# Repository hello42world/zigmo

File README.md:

# Intro
ZigMo is a 4 channel Zigbee soil moisture meter.  The project pursues 2 goals:
* Hardware: Attempt some very basic electric engineering and build a Zigbee device based on a custom PCB.
* Software: Write a custom firmware for the device that would make the Zigbee thing work.  

# Description
The concept is pretty simple. It is a Zigbee end device with 4 capacitive wire connected moisture sensors that you could stick into 4 nearby flower pots and monitor moisture levels in all of them with a single device.

This is what it looks like in Home Assistant:

The device is based on a popular CC2530 module that can be bought off Aliexpress for about $3. Custom PCB part handles battery power, routes connections to individual moisture sensors, provides debug connectors and implements user interface - a LED and a button.

# Build notes
### PCB:
The PCB was designed in KiCad and then ordered from JLCPCB. All parts are common and can be ordered from your favorite parts supplier.

**Note**: I know nothing about electric engineering and have no experience with PCB design. I just watched some video on Youtube on how to do it.

### Firmware:
The firmware is based on Zstack 3.0.2. It simply queries the moisture sensors and measures battery voltage every 5 minutes.

ZStack SDK is available for free from Texas Instruments. It contains several examples and even a guide on how to branch your own project off one of those examples (Z-Stack 3.0 Sample Application User's Guide.pdf). 
The most challenging part IMO is getting the IDE/Compiler. ZStack 3.0.2 applications should be built using IAR studio for 8051 processors version 10.20. This IDE is not free, however a free trial is available. You may find other ways of getting it if you search hard enough.

# See also
- Book: Drew Gislason - "Zigbee Wireless Networking"
- Very cool and super detailed series of posts on how to build a Zigbee device from scratch based on the NXP Zigbee stack: https://github.com/grafalex82/hellozigbee
- A bunch of ZStack Zigbee projects built at very professional level: https://github.com/diyruz

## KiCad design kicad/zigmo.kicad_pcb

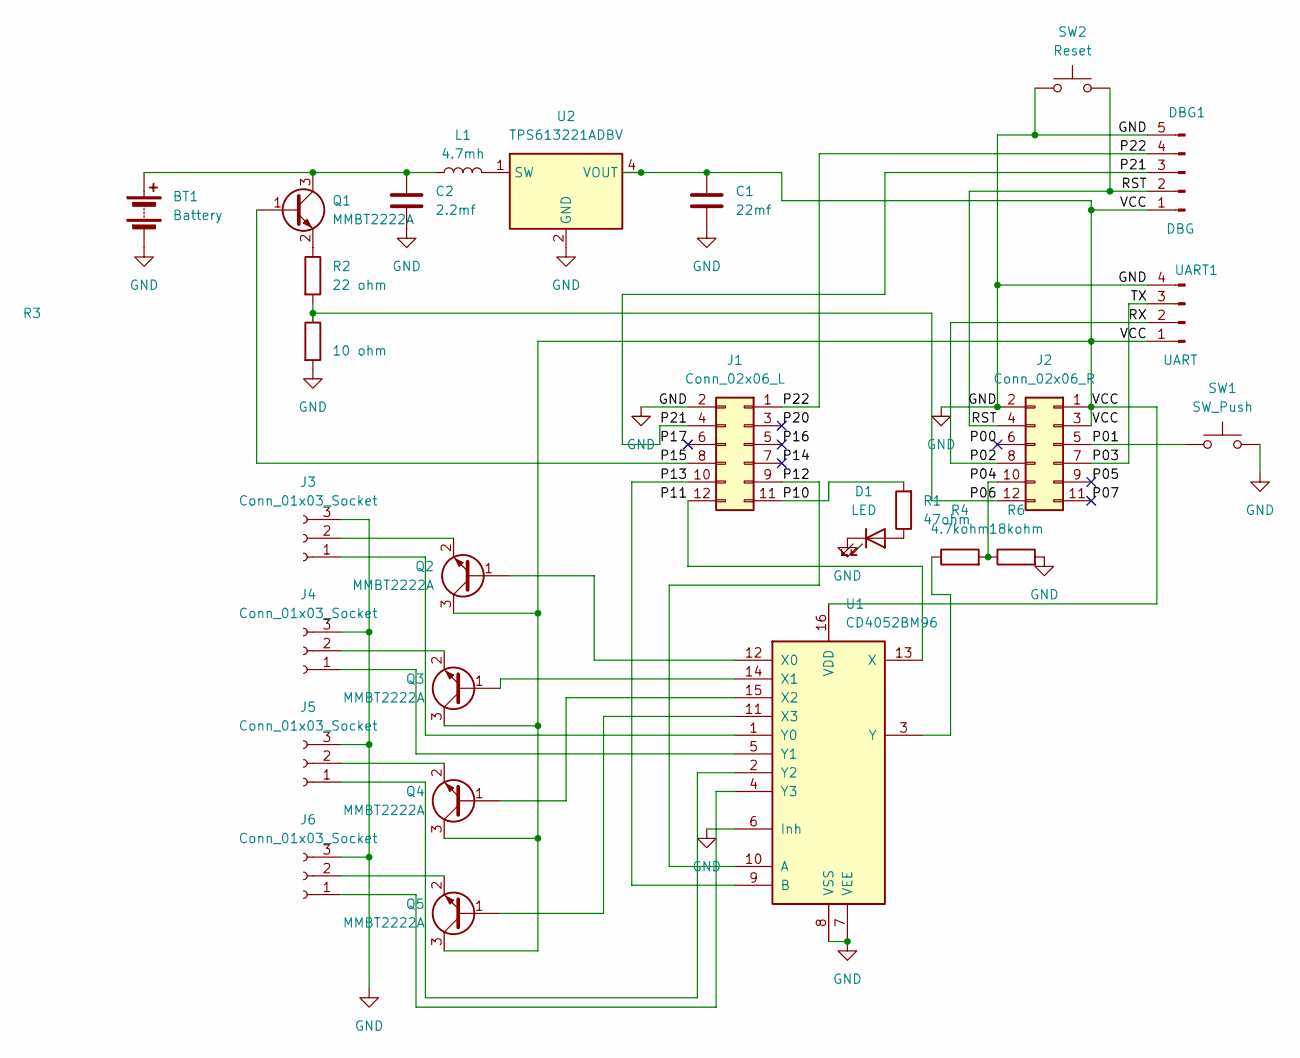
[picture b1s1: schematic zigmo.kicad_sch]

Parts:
BT1: Battery; BatteryHolder_Keystone_2462_2xAA
C1: 22mf; C_0805_2012Metric_Pad1.18x1.45mm_HandSolder
C2: 2.2mf; C_0805_2012Metric_Pad1.18x1.45mm_HandSolder
D1: LED; LED_D3.0mm
DBG1: DBG; PinHeader_1x05_P2.54mm_Vertical
J1: Conn_02x06_L; PinSocket_2x06_P2.54mm_Vertical
J2: Conn_02x06_R; PinSocket_2x06_P2.54mm_Vertical
J3, J4, J5, J6: Conn_01x03_Socket; JST_XH_B3B-XH-A_1x03_P2.50mm_Vertical
L1: 4.7mh; L_1008_2520Metric_Pad1.43x2.20mm_HandSolder
Q1, Q2, Q3, Q4, Q5: MMBT2222A; SOT-23
R1: 47ohm; R_0805_2012Metric_Pad1.20x1.40mm_HandSolder
R2: 22 ohm; R_0805_2012Metric_Pad1.20x1.40mm_HandSolder
R3: 10 ohm; R_0805_2012Metric_Pad1.20x1.40mm_HandSolder
R4: 4.7kohm; R_0805_2012Metric_Pad1.20x1.40mm_HandSolder
R6: 18kohm; R_0805_2012Metric_Pad1.20x1.40mm_HandSolder
SW1: SW_Push; SW_SPST_B3U-1000P
SW2: Reset; SW_SPST_B3U-1000P
U1: CD4052BM96; SO-16_3.9x9.9mm_P1.27mm
U2: TPS613221ADBV; SOT-23-5
UART1: UART; PinHeader_1x04_P2.54mm_Vertical

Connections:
/P00: J2.6
/P01: J2.5, SW1.1
/P02: J2.8, UART1.2; also elsewhere on the board
/P03: J2.7, UART1.3; also elsewhere on the board
/P04: J2.10, R4.2, R6.1
/P05: J2.9
/P06: J2.12, R2.2, R3.1
/P07: J2.11
/P10: J1.11, R1.2
/P11: J1.12, U1.13 (X)
/P12: J1.9, U1.10 (A)
/P13: J1.10, U1.9 (B)
/P14: J1.7
/P15: J1.8, Q1.1 (B)
/P16: J1.5
/P17: J1.6
/P20: J1.3
/P21: DBG1.3, J1.4; also elsewhere on the board
/P22: DBG1.4, J1.1; also elsewhere on the board
/RST: DBG1.2, J2.4, SW2.2; also elsewhere on the board
/VCC: C1.1, DBG1.1, J2.1, J2.3, Q2.3 (C), Q3.3 (C), Q4.3 (C), Q5.3 (C), U1.16 (VDD), U2.4 (VOUT), UART1.1; also elsewhere on the board
GND: BT1.2 (-), C1.2, C2.2, D1.1 (K), DBG1.5, J1.2, J2.2, J3.3, J4.3, J5.3, J6.3, R3.2, R6.2, SW1.2, SW2.1, U1.6 (Inh), U1.7 (VEE), U1.8 (VSS), U2.2 (GND), UART1.4; also elsewhere on the board
unnamed: BT1.1 (+), C2.1, L1.1, Q1.3 (C)
unnamed: D1.2 (A), R1.1
unnamed: J3.1, U1.1 (Y0)
unnamed: J3.2, Q2.2 (E)
unnamed: J4.1, U1.5 (Y1)
unnamed: J4.2, Q3.2 (E)
unnamed: J5.1, U1.2 (Y2)
unnamed: J5.2, Q4.2 (E)
unnamed: J6.1, U1.4 (Y3)
unnamed: J6.2, Q5.2 (E)
unnamed: Q1.2 (E), R2.1
unnamed: Q2.1 (B), U1.12 (X0)
unnamed: Q3.1 (B), U1.14 (X1)
unnamed: Q4.1 (B), U1.15 (X2)
unnamed: Q5.1 (B), U1.11 (X3)
unnamed: R4.1, U1.3 (Y)
unnamed: L1.2, U2.1 (SW)

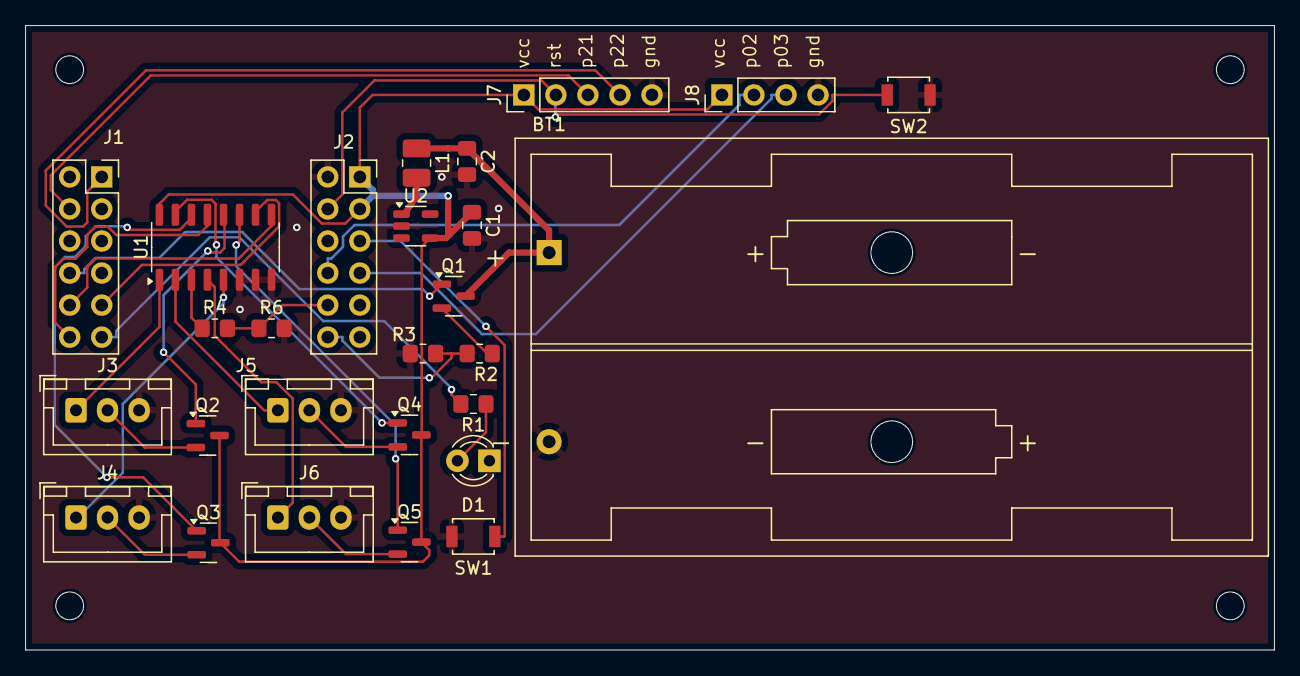
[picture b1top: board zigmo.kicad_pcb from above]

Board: 2 copper layers, 99.0 x 49.5 mm, 31 parts (0 on the bottom side), 32 nets.

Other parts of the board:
J7: DBG; PinHeader_1x05_P2.54mm_Vertical
J8: UART; PinHeader_1x04_P2.54mm_Vertical
REF1, REF2, REF3, REF4: MountingHole_2.2mm_M2

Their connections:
/P02: J8.2; also elsewhere on the board
/P03: J8.3; also elsewhere on the board
/P21: J7.3; also elsewhere on the board
/P22: J7.4; also elsewhere on the board
/RST: J7.2; also elsewhere on the board
/VCC: J7.1, J8.1; also elsewhere on the board
GND: J7.5, J8.4; also elsewhere on the board

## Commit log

2024-07-02 Try running all endpoints in 1 task
2024-07-03 Initial sketch of sensor array code
2024-07-03 Code cleanup
2024-07-03 Try multiple sensors in array
2024-07-07 Sensor value update works (dummy)
2024-07-29 Dummy attr update (on timer)
2024-07-29 Custom HAL compiles (not tested)
2024-07-30 debug stuff
2024-08-04 Restart button impl with fresh HAL copy
2024-08-13 Played with a button and a led
2024-08-13 Unused file removed
2024-08-14 Button scan fix + code cleanup
2024-08-14 unused file removed from project
2024-08-15 Button long press implemented
2024-08-17 Network joining added
2024-09-22 Played with ADC
2024-09-22 Some code cleanup
2024-10-13 Test using ADC AIN7 ref + code cleanup.
2024-10-13 Set ADC ref in read function.
2024-10-13 Added delay function to utils
2024-10-13 Played with batt voltage meter
2024-10-16 Batt measuring sketched
2024-10-16 Reenabled join btn
2024-10-16 Battery measuring enabled
2024-10-20 Joystick stuff removed from HAL.
2024-10-20 Removed dependency on hal_key.h
2024-10-20 Minor cleanup
2024-10-20 More code cleanup.
2024-11-03 debug print added
2024-11-04 Button handling reworked
2024-11-05 Minor code cleanup
2024-11-07 Moved stuff around
2024-11-07 All sensor code extracted
2024-11-09 Led blink implemented
2025-01-16 Code cleanup and fixes.
2025-01-23 Fix binding array size
2025-01-23 Some skeleton code added
2025-01-23 Data struct init implemented
2025-01-23 Tried addind a second sensor
2025-01-23 Dummy humidity cluster added
2025-01-23 Mem optimized. XDATA error gone.
2025-01-23 Disable flow contol in MT
2025-01-23 Renames in code.
2025-01-23 Files renamed
2025-01-24 Set initial measured value to 0
2025-01-26 KiCad files added
2025-01-26 zigbee2mqtt external converter added
2025-01-26 Quick readme added.
